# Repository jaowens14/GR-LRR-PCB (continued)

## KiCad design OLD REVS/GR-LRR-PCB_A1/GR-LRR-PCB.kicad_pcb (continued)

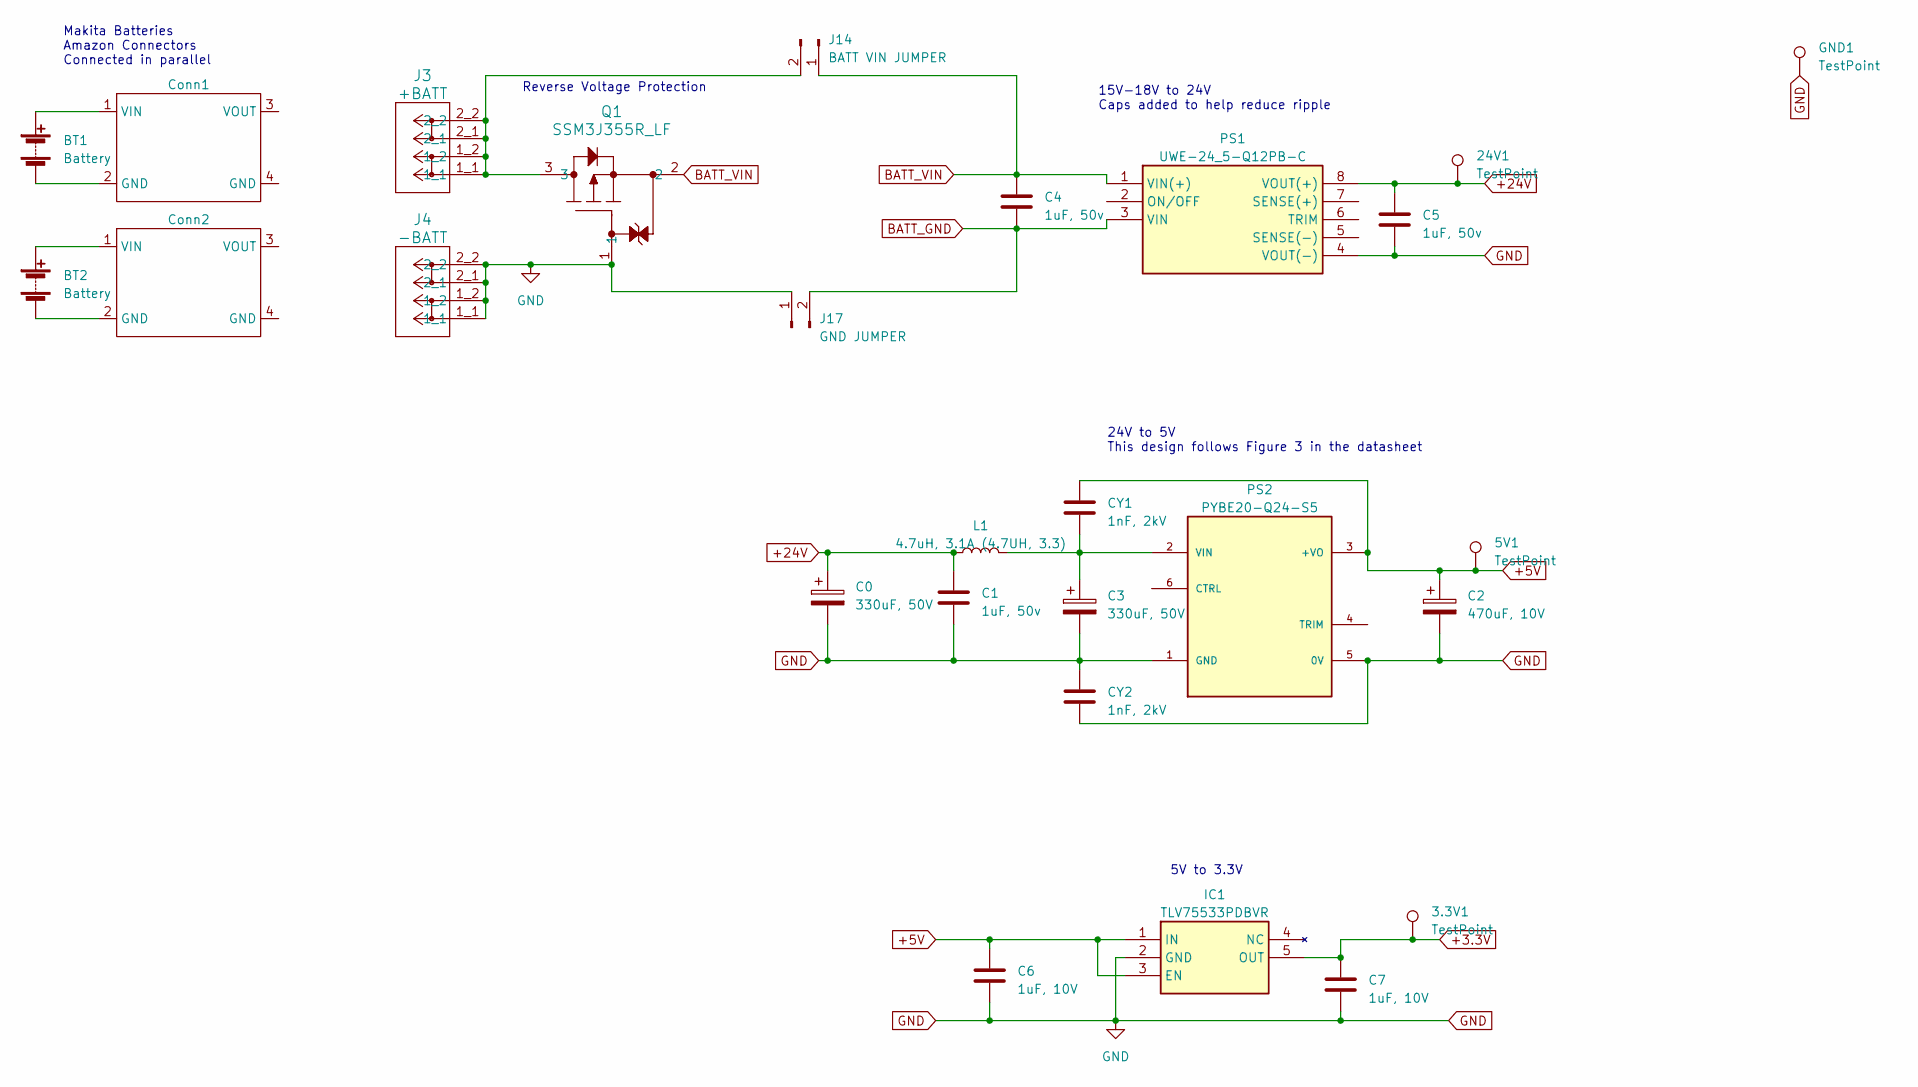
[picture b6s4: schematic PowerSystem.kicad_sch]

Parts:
3.3V1, 5V1, 24V1: TestPoint; TestPoint_Pad_D2.5mm
BT1, BT2: Battery
C0, C3: 330uF, 50V; CP_Radial_D10.0mm_P5.00mm; Part Number ECA-1HM331B
C1, C4, C5: 1uF, 50v; C_0805_2012Metric_Pad1.18x1.45mm_HandSolder; Part Number CL21B105KBFNNNG
C2: 470uF, 10V; CP_EIA-7343-15_Kemet-W_Pad2.25x2.55mm_HandSolder; Part Number 293D477X9010E2TE3
C6, C7: 1uF, 10V; C_0805_2012Metric_Pad1.18x1.45mm_HandSolder; Part Number CL21B105KPFNNNE
CY1, CY2: 1nF, 2kV; C_1812_4532Metric_Pad1.57x3.40mm_HandSolder; Part Number C1812C102KGRACAUTO
Conn1, Conn2: (no value)
GND1: TestPoint; TestPoint_Pad_D2.5mm
IC1: TLV75533PDBVR; SOT95P280X145-5N; Mouser Part Number 595-TLV75533PDBVR
J3: +BATT; 2604-1102
J4: -BATT; 2604-1102
J14: BATT VIN JUMPER; PinHeader_1x02_P2.54mm_Vertical
J17: GND JUMPER; PinHeader_1x02_P2.54mm_Vertical
L1: 4.7uH, 3.1A (4.7UH, 3.3); IND_XGL4018_COC-M; Part Number XGL4018-472MEC
PS1: UWE-24_5-Q12PB-C; UWE245Q12PBC; Mouser Part Number 580-UWE-24/5-Q12PB-C
PS2: PYBE20-Q24-S5; CONV_PYBE20-Q24-S5
Q1: SSM3J355R_LF; SOT-23F_TOS

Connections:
+3.3V: 3.3V1.1, C7.1, IC1.5 (OUT); also elsewhere on the board
+5V: 5V1.1, C2.1, C6.1, CY1.1, IC1.1 (IN), IC1.3 (EN), PS2.3 (+VO); also elsewhere on the board
+24V: 24V1.1, C0.1, C1.1, C5.1, L1.1, PS1.8 (VOUT(+)); also elsewhere on the board
BATT_GND: C4.2, J17.2, PS1.3 (VIN)
BATT_VIN: C4.1, J14.1, PS1.1 (VIN(+)), Q1.2; also elsewhere on the board
GND: C0.2, C1.2, C2.2, C3.2, C5.2, C6.2, C7.2, CY2.1, CY2.2, GND1.1, IC1.2 (GND), J4.1_1, J4.1_2, J4.2_1, J4.2_2, J17.1, PS1.4 (VOUT(-)), PS2.1 (GND), PS2.5 (0V), Q1.1; also elsewhere on the board
unnamed: BT1.1 (+), Conn1.1 (VIN)
unnamed: BT1.2 (-), Conn1.2 (GND)
unnamed: BT2.1 (+), Conn2.1 (VIN)
unnamed: BT2.2 (-), Conn2.2 (GND)
unnamed: J3.1_1, J3.1_2, J3.2_1, J3.2_2, J14.2, Q1.3
unnamed: C3.1, CY1.2, L1.2, PS2.2 (VIN)

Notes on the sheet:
Makita Batteries Amazon Connectors Connected in parallel
5V to 3.3V
15V-18V to 24V Caps added to help reduce ripple
Reverse Voltage Protection
24V to 5V This design follows Figure 3 in the datasheet

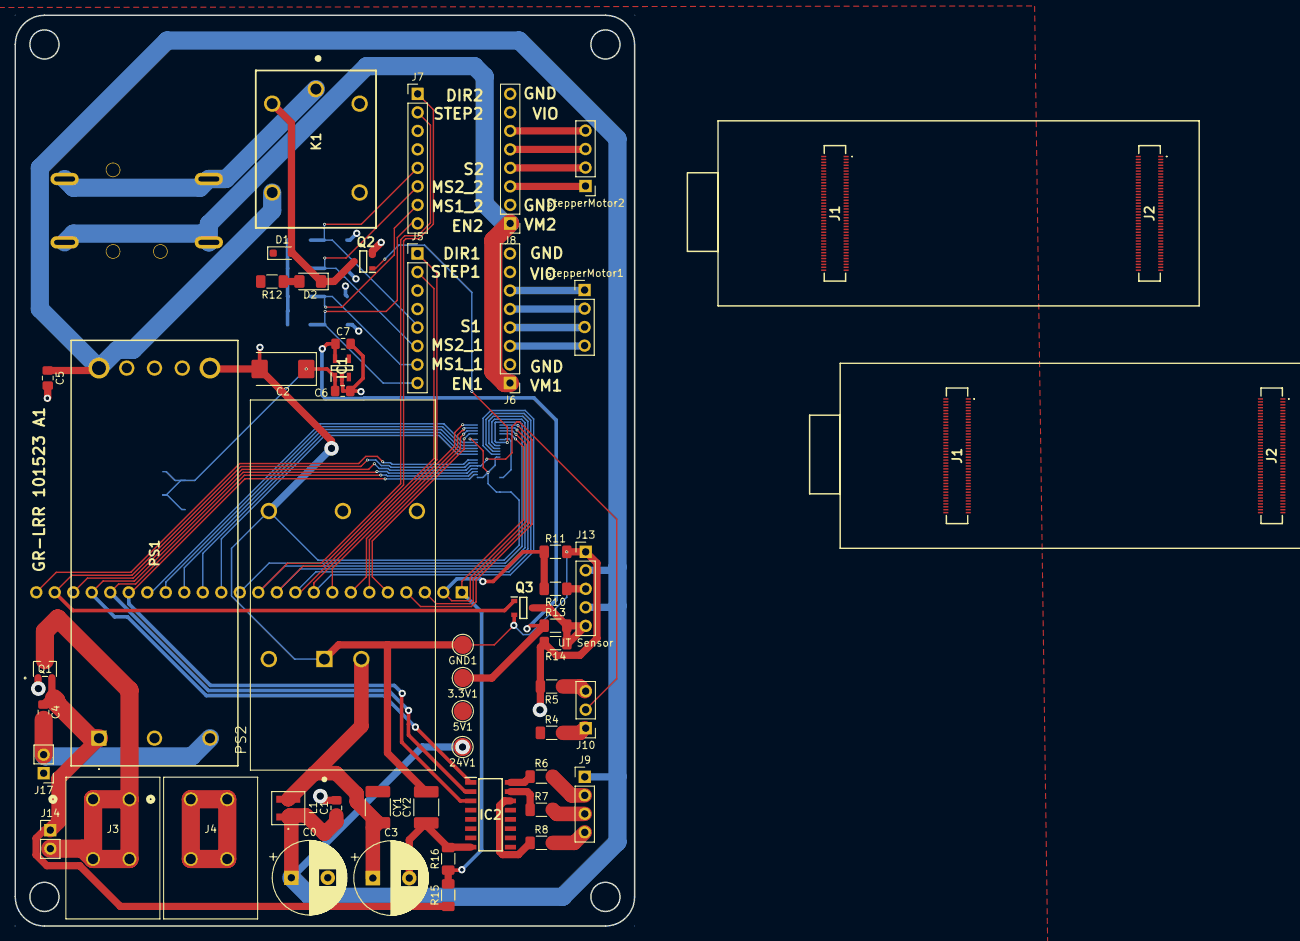
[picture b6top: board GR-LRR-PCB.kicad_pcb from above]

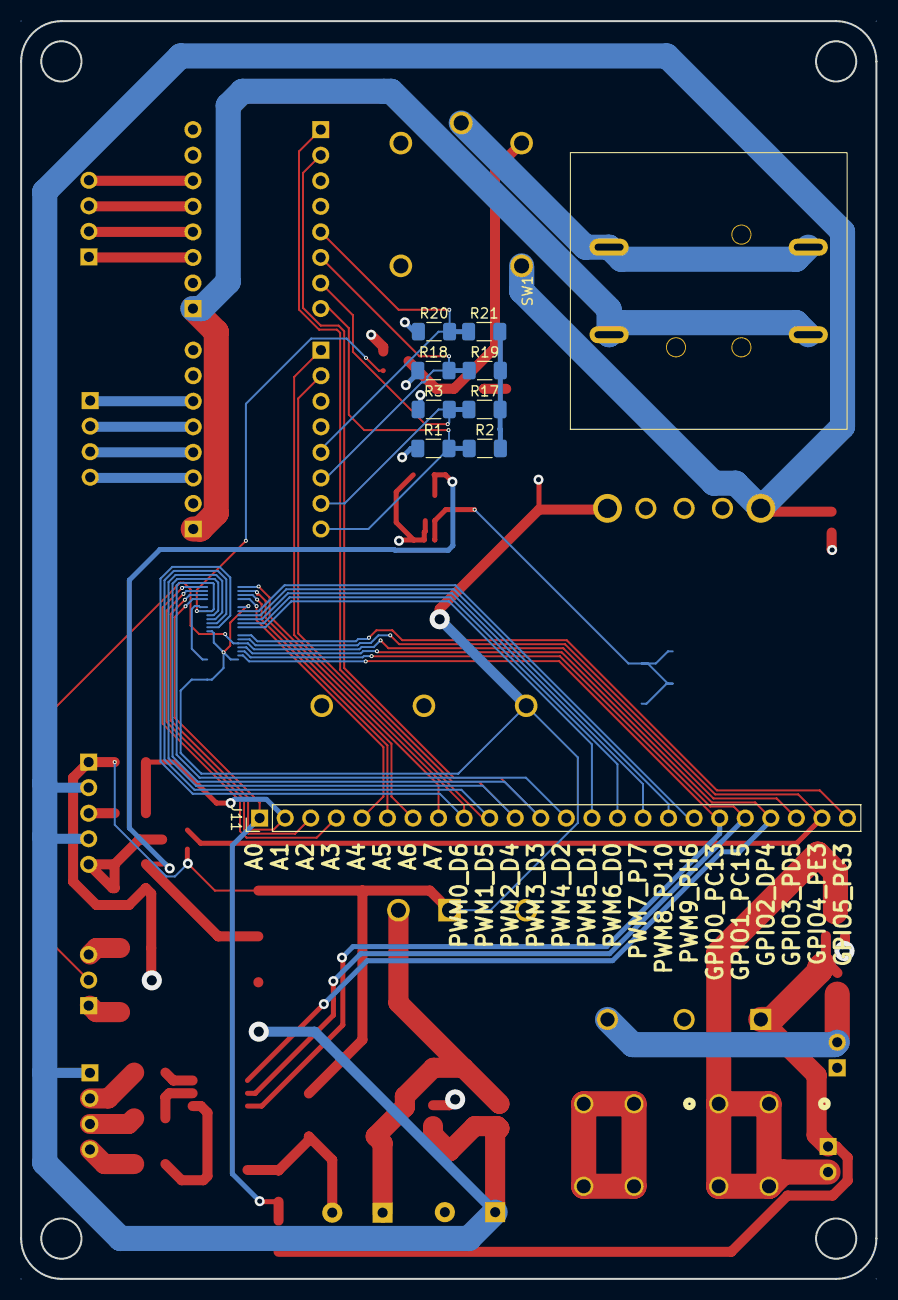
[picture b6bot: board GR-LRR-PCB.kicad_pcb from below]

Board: 2 copper layers, 85.0 x 125.0 mm, 64 parts (10 on the bottom side), 59 nets.

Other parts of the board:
J1#2, J2#2: DF40HC3.5-80DS-0.4V51; DF40HC3580DS04V58

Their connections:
46_GPIO0_PC13: J2#2.46; also elsewhere on the board
48_GPIO1_PC15: J2#2.48; also elsewhere on the board
50_GPIO2_PD4: J2#2.50; also elsewhere on the board
52_GPIO3_PD5: J2#2.52; also elsewhere on the board
54_GPIO4_PE3: J2#2.54; also elsewhere on the board
56_GPIO5_PG3: J2#2.56; also elsewhere on the board
58_GPIO6_PG10: J2#2.58; also elsewhere on the board
59_PWM0_D6: J2#2.59; also elsewhere on the board
60_PWM5_D1: J2#2.60; also elsewhere on the board
61_PWM1_D5: J2#2.61; also elsewhere on the board
62_PWM6_D0: J2#2.62; also elsewhere on the board
63_PWM2_D4: J2#2.63; also elsewhere on the board
64_PWM7_PJ7: J2#2.64; also elsewhere on the board
65_PWM3_D3: J2#2.65; also elsewhere on the board
66_PWM8_PJ10: J2#2.66; also elsewhere on the board
67_PWM4_D2: J2#2.67; also elsewhere on the board
68_PWM9_PH6: J2#2.68; also elsewhere on the board
73_ANALOG_A0: J2#2.73; also elsewhere on the board
74_ANALOG_A4: J2#2.74; also elsewhere on the board
75_ANALOG_A1: J2#2.75; also elsewhere on the board
76_ANALOG_A5: J2#2.76; also elsewhere on the board
77_ANALOG_A2: J2#2.77; also elsewhere on the board
78_ANALOG_A6: J2#2.78; also elsewhere on the board
79_ANALOG_A3: J2#2.79; also elsewhere on the board
80_ANALOG_A7: J2#2.80; also elsewhere on the board
+5V: J1#2.21, J1#2.32, J1#2.41, J1#2.48; also elsewhere on the board
GND: J2#2.33, J2#2.44, J2#2.57, J2#2.70; also elsewhere on the board

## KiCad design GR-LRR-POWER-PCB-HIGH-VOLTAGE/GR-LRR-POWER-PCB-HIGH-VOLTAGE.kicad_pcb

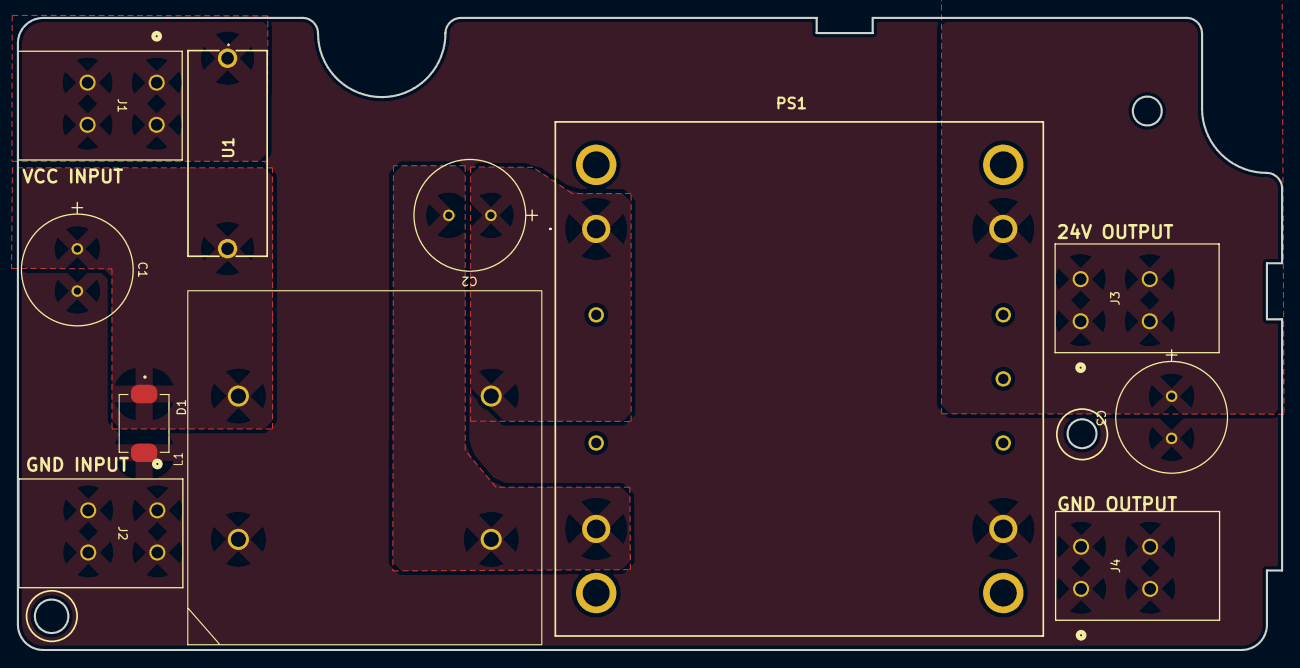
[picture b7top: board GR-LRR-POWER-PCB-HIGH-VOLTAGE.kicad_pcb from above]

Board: 2 copper layers, 150.0 x 75.0 mm, 11 parts (0 on the bottom side), 6 nets, no tracks yet.

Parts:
C1, C2, C3: 100PX220MEFC12.5X20; CAP_PK&slash_PZ_12P5X20_LOW_RUB
D1: SMCJ40A; DIOM7959X262N
J1: BATT+; 2604
J2, J4: GND; 2604
J3: 24V; 2604
L1: SC-14-15JH
PS1: QSB30024S24
U1: 696108003002; WR-FSH_THT_2

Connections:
+24V: C3.1, J3.1_1, J3.1_2, J3.2_1, J3.2_2, PS1.9 (+VOUT)
BATT+: C1.1, D1.C, L1.2 (1N2), U1.2
GND: C1.2, C3.2, D1.A, J2.1_1, J2.1_2, J2.2_1, J2.2_2, J4.1_1, J4.1_2, J4.2_1, J4.2_2, L1.1 (1N1), PS1.5 (-VOUT)
unnamed: J1.1_1, J1.1_2, J1.2_1, J1.2_2, U1.1
unnamed: C2.2, L1.4 (2N1), PS1.4 (-VIN)
unnamed: C2.1, L1.3 (2N2), PS1.1 (+VIN)

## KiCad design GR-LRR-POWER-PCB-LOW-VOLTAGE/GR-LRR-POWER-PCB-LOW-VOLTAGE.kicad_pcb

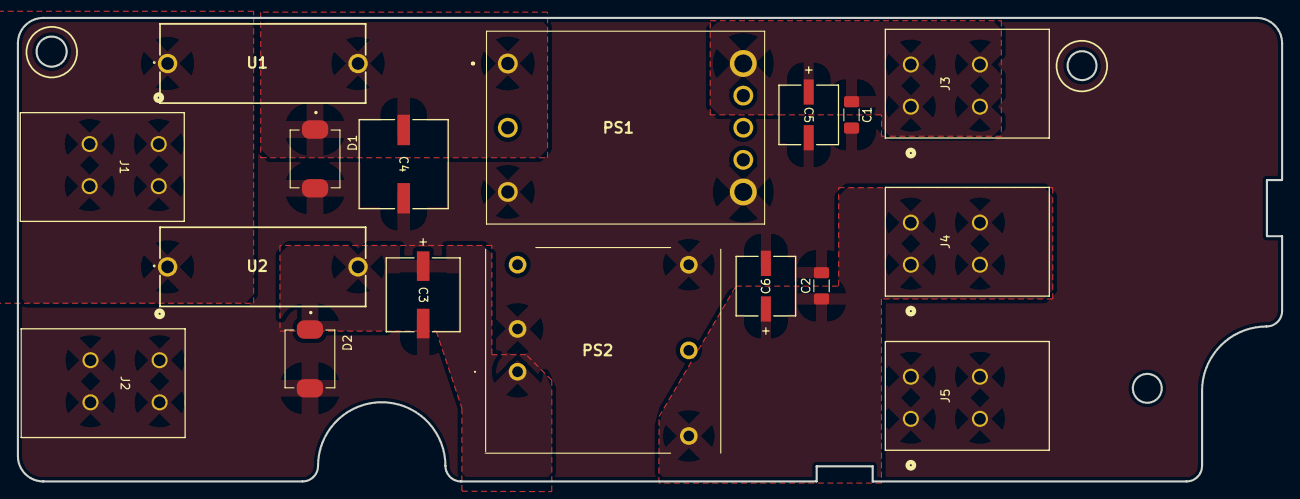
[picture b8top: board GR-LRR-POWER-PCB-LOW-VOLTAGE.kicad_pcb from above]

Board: 2 copper layers, 150.0 x 55.0 mm, 17 parts (0 on the bottom side), 6 nets, no tracks yet.

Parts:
C1, C2: 1uF : CL31B105KCHNNNE; C_1206_3216Metric_Pad1.33x1.80mm_HandSolder
C3: 100uF : UWT1H101MNL1GS; PCAP_8x10-ELECT_NCA
C4: 220uF : UWT1H221MNL1GS; U2-R_NCH
C5, C6: 10uF : UWZ1H100MCL1GB; PCAP_6.3x5.4-ELECT_NCA
D1, D2: SMCJ40A; DIOM7959X262N
J1: BATT+; 2604-1102
J2: BATT-; 2604-1102
J3: 5V; 2604-1102
J4: 3.3V; 2604-1102
J5: GND; 2604-1102
PS1: UWS-510-Q12P-C
PS2: UEI15-033-Q12P-C; UEI15033Q12PC
U1, U2: 696108003002; WR-FSH_THT_2

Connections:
BATT+: J1.1_1, J1.1_2, J1.2_1, J1.2_2, U1.1, U2.1
GND: C1.2, C2.2, C3.2, C4.2, C5.2, C6.2, D1.A, D2.A, J2.1_1, J2.1_2, J2.2_1, J2.2_2, J5.1_1, J5.1_2, J5.2_1, J5.2_2, PS1.3 (-VIN), PS1.4 (-VOUT), PS2.2 (-VIN), PS2.5 (-VOUT)
unnamed: C4.1, D1.C, PS1.1 (+VIN), U1.2
unnamed: C1.1, C5.1, J3.1_1, J3.1_2, J3.2_1, J3.2_2, PS1.8 (+VOUT)
unnamed: C3.1, D2.C, PS2.1 (+VIN), U2.2
unnamed: C2.1, C6.1, J4.1_1, J4.1_2, J4.2_1, J4.2_2, PS2.3 (+VOUT)

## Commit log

2023-10-13 need to add more blocks
2023-10-17 selected parts for power side
2023-10-23 starting first layout
2023-10-23 save
2023-10-25 new smaller layout
2023-10-25 new gerbers
2023-10-31 added step files
2023-12-06 power and control boards
2024-03-15 moving to two enclosures
2024-03-25 low and high V boards done
2024-05-09 purchasing A3 power
2024-05-12 finished routing
2024-05-13 ordered power and control A4
2024-08-06 upload
2024-08-26 saver
